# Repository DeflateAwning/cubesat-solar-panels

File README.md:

# cubesat-solar-panels
A quick design of solar panels for a cubesat using KiCAD

## License
CERN Open Hardware Licence Version 2 - Permissive

[CERN OHL v2 Permissive on ChooseALicense.com](https://choosealicense.com/licenses/cern-ohl-p-2.0/)

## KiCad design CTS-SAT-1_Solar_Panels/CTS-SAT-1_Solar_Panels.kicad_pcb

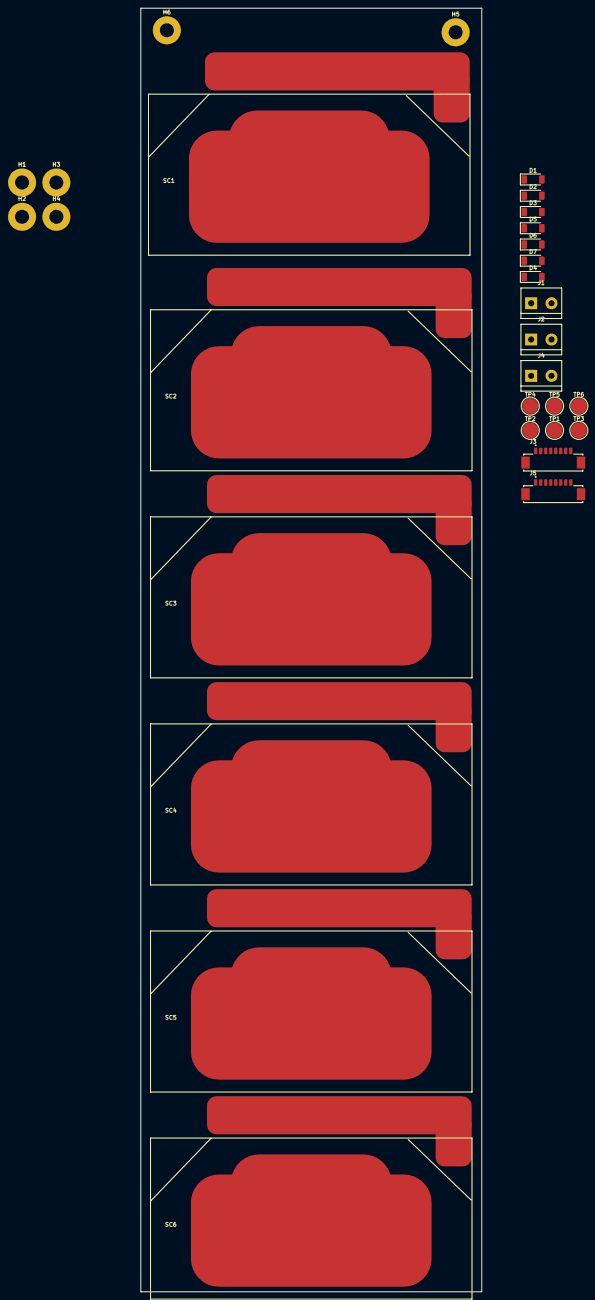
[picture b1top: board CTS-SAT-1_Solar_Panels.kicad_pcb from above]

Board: 2 copper layers, 85.0 x 320.0 mm, 30 parts (0 on the bottom side), 7 nets, no tracks yet.

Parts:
D1, D2, D3, D4, D5, D6, D7: PMEG3050EP; D_SOD-128
H1, H2, H3, H4, H5, H6: MountingHole_Pad; MountingHole_3.5mm_Pad
J1, J2, J4: Screw_Terminal_01x02; TerminalBlock_bornier-2_P5.08mm
J3, J5: 0532610871; MOLEX_0532610871
SC1, SC2, SC3, SC4, SC5, SC6: Solar_Cell; Shyim_Cell
TP1, TP2, TP3, TP4, TP5, TP6: TestPoint; TestPoint_Pad_D4.0mm

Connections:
+VDC: D4.1 (K), J1.2, J2.2, J3.1, J3.2, J3.5, J3.6, J4.2, J5.1, J5.2, J5.5, J5.6
GND: D3.2 (A), D7.2 (A), H1.1, H2.1, H3.1, H4.1, H5.1, H6.1, J1.1, J2.1, J3.3, J3.4, J3.7, J3.8, J4.1, J5.3, J5.4, J5.7, J5.8, SC3.2 (-), SC6.2 (-), TP3.1
unnamed: D1.2 (A), D2.1 (K), SC1.2 (-), SC2.1 (+), TP2.1
unnamed: D1.1 (K), D4.2 (A), D5.1 (K), SC1.1 (+), SC4.1 (+), TP4.1
unnamed: D2.2 (A), D3.1 (K), SC2.2 (-), SC3.1 (+), TP1.1
unnamed: D5.2 (A), D6.1 (K), SC4.2 (-), SC5.1 (+), TP5.1
unnamed: D6.2 (A), D7.1 (K), SC5.2 (-), SC6.1 (+), TP6.1

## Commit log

2024-01-15 Add CERN OHL v2 Permissive license
2024-01-15 Add current version of solar panel design
